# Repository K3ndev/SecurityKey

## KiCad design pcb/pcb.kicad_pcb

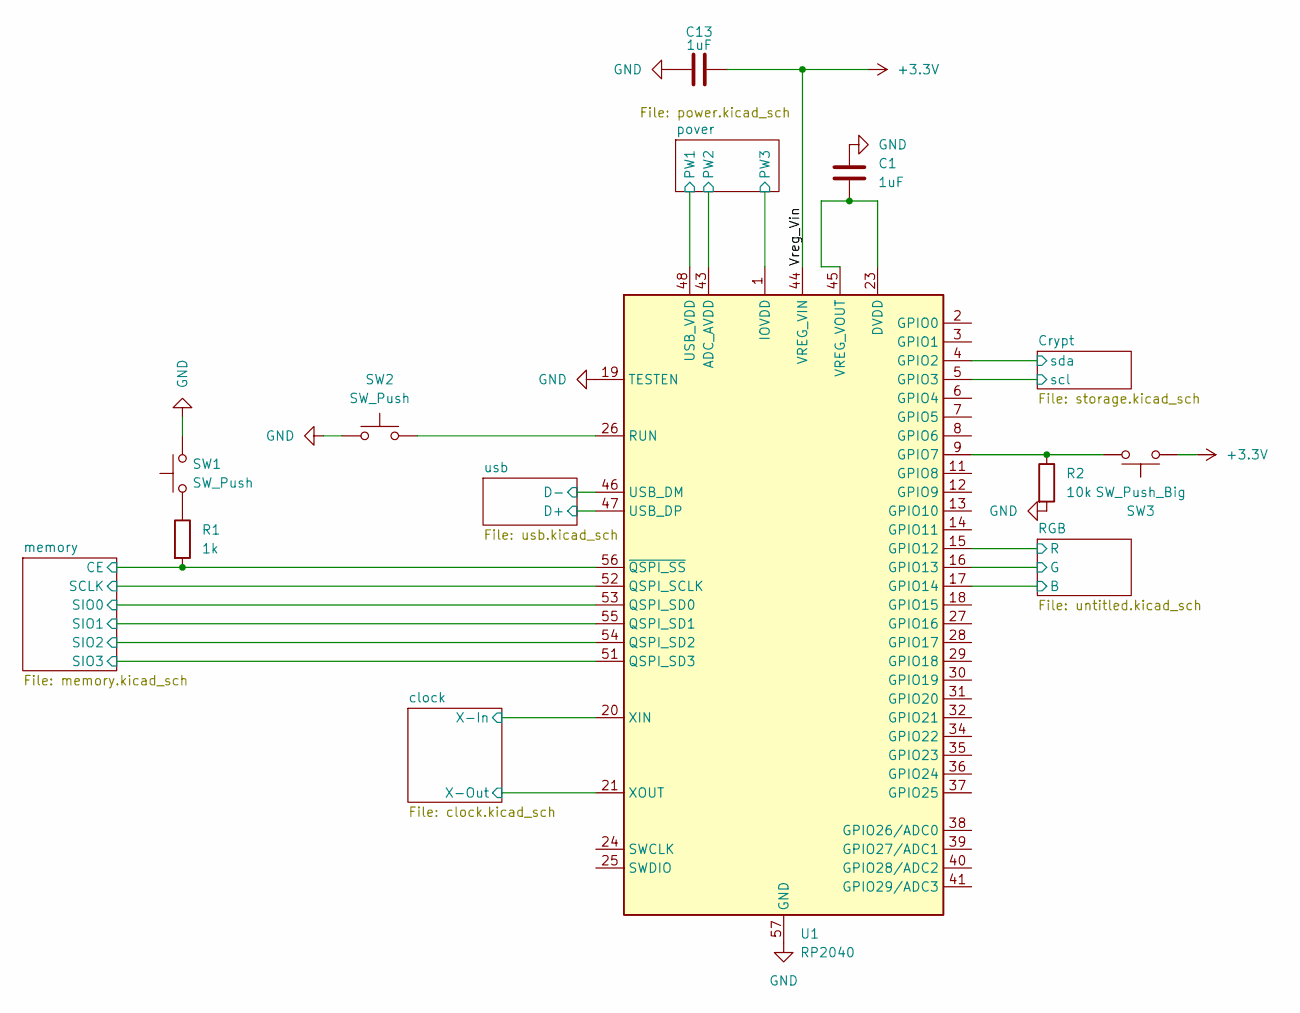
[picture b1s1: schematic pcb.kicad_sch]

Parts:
C1: 1uF; C_0603_1608Metric; LCSC Part C1592
C13: 1uF; C_0603_1608Metric; LCSC Part C1591
R1: 1k; R_0603_1608Metric; LCSC Part C22548
R2: 10k; R_0603_1608Metric; LCSC Part C98220
SW1, SW2: SW_Push; SW-SMD_L3.9-W3.0-P4.45; LCSC Part C115357
SW3: SW_Push_Big; SW-SMD_L3.9-W3.0-P4.45; LCSC Part C115357
U1: RP2040; QFN-56-1EP_7x7mm_P0.4mm_EP3.2x3.2mm; LCSC Part C2040

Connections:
+3.3V: C13.2, SW3.2, U1.1 (IOVDD), U1.10 (IOVDD), U1.22 (IOVDD), U1.33 (IOVDD), U1.42 (IOVDD), U1.43 (ADC_AVDD), U1.44 (VREG_VIN), U1.48 (USB_VDD), U1.49 (IOVDD); also elsewhere on the board
/Crypt/scl: U1.5 (GPIO3); also elsewhere on the board
/Crypt/sda: U1.4 (GPIO2); also elsewhere on the board
/RGB/B: U1.17 (GPIO14); also elsewhere on the board
/RGB/G: U1.16 (GPIO13); also elsewhere on the board
/RGB/R: U1.15 (GPIO12); also elsewhere on the board
/clock/X-In: U1.20 (XIN); also elsewhere on the board
/clock/X-Out: U1.21 (XOUT); also elsewhere on the board
/memory/CE: R1.2, U1.56 (~QSPI_SS); also elsewhere on the board
/memory/SCLK: U1.52 (QSPI_SCLK); also elsewhere on the board
/memory/SIO0: U1.53 (QSPI_SD0); also elsewhere on the board
/memory/SIO1: U1.55 (QSPI_SD1); also elsewhere on the board
/memory/SIO2: U1.54 (QSPI_SD2); also elsewhere on the board
/memory/SIO3: U1.51 (QSPI_SD3); also elsewhere on the board
/usb/D+: U1.47 (USB_DP); also elsewhere on the board
/usb/D-: U1.46 (USB_DM); also elsewhere on the board
GND: C1.2, C13.1, R2.2, SW1.2, SW2.1, U1.19 (TESTEN), U1.57 (GND); also elsewhere on the board
unnamed: R1.1, SW1.1
unnamed: R2.1, SW3.1, U1.9 (GPIO7)
unnamed: SW2.2, U1.26 (RUN)
unnamed: C1.1, U1.23 (DVDD), U1.45 (VREG_VOUT), U1.50 (DVDD)

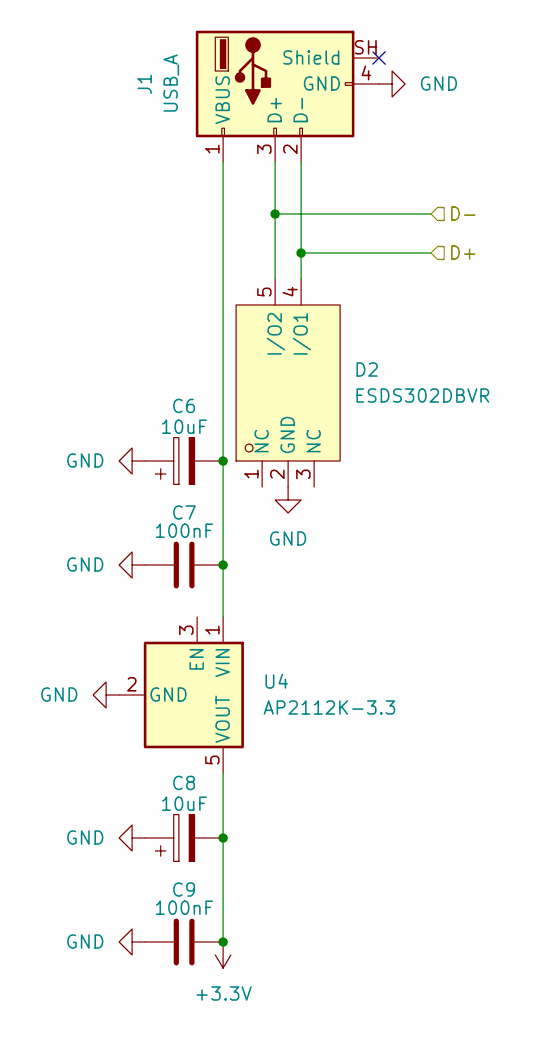
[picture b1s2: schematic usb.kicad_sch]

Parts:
C6, C8: 10uF; C_0603_1608Metric; LCSC Part C19702
C7, C9: 100nF; C_0603_1608Metric; LCSC Part C1591
D2: ESDS302DBVR; SOT-23-5_L3.0-W1.6-P0.95-LS2.8-BL; MPN ESDS302DBVR; LCSC Part C1975280
J1: USB_A; USB_A_PCB_Edge_receptacle
U4: AP2112K-3.3; SOT-23-5; LCSC Part C51118

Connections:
+3.3V: C8.2, C9.2, U4.5 (VOUT); also elsewhere on the board
/usb/D+: D2.4 (I/O1), J1.2 (D-); also elsewhere on the board
/usb/D-: D2.5 (I/O2), J1.3 (D+); also elsewhere on the board
GND: C6.1, C7.1, C8.1, C9.1, D2.2 (GND), J1.4 (GND), U4.2 (GND); also elsewhere on the board
unnamed: C6.2, C7.2, J1.1 (VBUS), U4.1 (VIN)

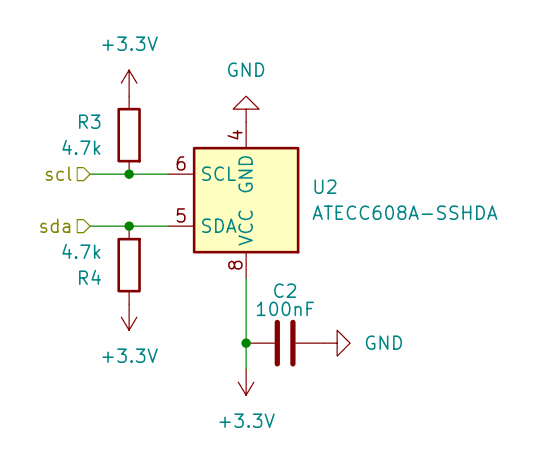
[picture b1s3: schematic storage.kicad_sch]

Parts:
C2: 100nF; C_0603_1608Metric; LCSC Part C1591
R3, R4: 4.7k; R_0603_1608Metric; LCSC Part C99782
U2: ATECC608A-SSHDA; SOIC-8_3.9x4.9mm_P1.27mm; LCSC Part C616024

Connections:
+3.3V: C2.1, R3.1, R4.1, U2.8 (VCC); also elsewhere on the board
/Crypt/scl: R3.2, U2.6 (SCL); also elsewhere on the board
/Crypt/sda: R4.2, U2.5 (SDA); also elsewhere on the board
GND: C2.2, U2.4 (GND); also elsewhere on the board

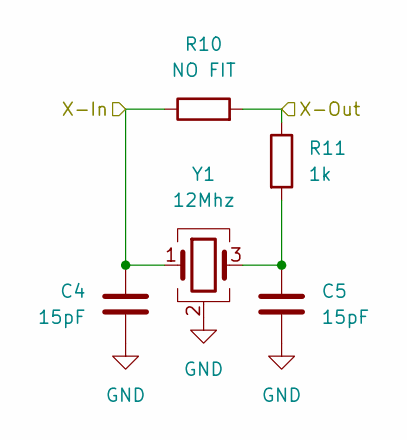
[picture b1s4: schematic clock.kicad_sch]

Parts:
C4, C5: 15pF; C_0603_1608Metric; LCSC Part C1644
R10: NO FIT; R_0603_1608Metric
R11: 1k; R_0603_1608Metric; LCSC Part C22548
Y1: 12Mhz; Crystal_SMD_3225-4Pin_3.2x2.5mm; LCSC Part C20625731

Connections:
/clock/X-In: C4.1, R10.1, Y1.1; also elsewhere on the board
/clock/X-Out: R10.2, R11.1; also elsewhere on the board
GND: C4.2, C5.2, Y1.2 (G), Y1.4 (G); also elsewhere on the board
unnamed: C5.1, R11.2, Y1.3

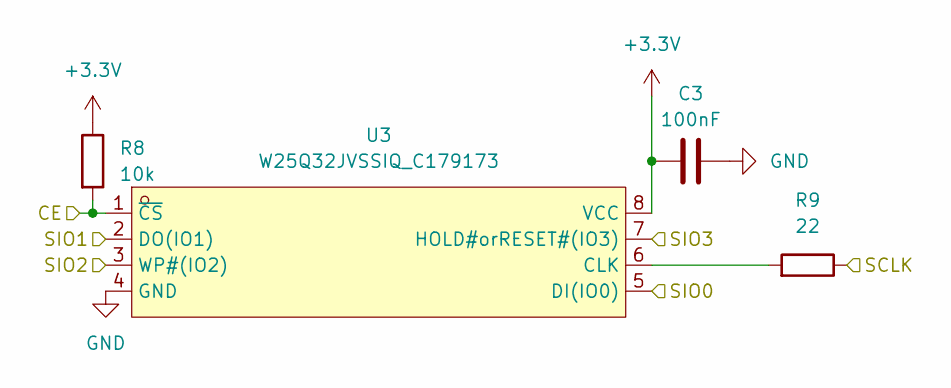
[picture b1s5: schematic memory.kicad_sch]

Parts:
C3: 100nF; C_0603_1608Metric; LCSC Part C1591
R8: 10k; R_0603_1608Metric; LCSC Part C98220
R9: 22; R_0603_1608Metric; LCSC Part C23345
U3: W25Q32JVSSIQ_C179173; SOIC-8_L5.3-W5.3-P1.27-LS8.0-BL; MPN W25Q32JVSSIQ; LCSC Part C179173

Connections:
+3.3V: C3.1, R8.1, U3.8 (VCC); also elsewhere on the board
/memory/CE: R8.2, U3.1 (~CS); also elsewhere on the board
/memory/SCLK: R9.1; also elsewhere on the board
/memory/SIO0: U3.5 (DI(IO0)); also elsewhere on the board
/memory/SIO1: U3.2 (DO(IO1)); also elsewhere on the board
/memory/SIO2: U3.3 (WP#(IO2)); also elsewhere on the board
/memory/SIO3: U3.7 (HOLD#orRESET#(IO3)); also elsewhere on the board
GND: C3.2, U3.4 (GND); also elsewhere on the board
unnamed: R9.2, U3.6 (CLK)

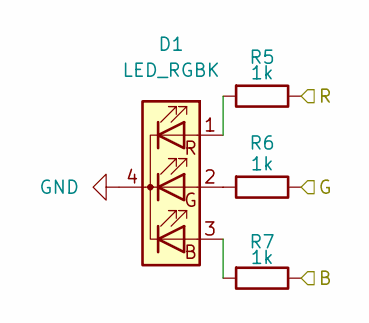
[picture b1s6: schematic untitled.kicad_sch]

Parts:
D1: LED_RGBK; LED_WS2812B_PLCC4_5.0x5.0mm_P3.2mm; LCSC Part C52917433
R5, R6, R7: 1k; R_0603_1608Metric; LCSC Part C22548

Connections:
/RGB/B: R7.1; also elsewhere on the board
/RGB/G: R6.1; also elsewhere on the board
/RGB/R: R5.1; also elsewhere on the board
GND: D1.4 (K); also elsewhere on the board
unnamed: D1.3 (BA), R7.2
unnamed: D1.2 (GA), R6.2
unnamed: D1.1 (RA), R5.2

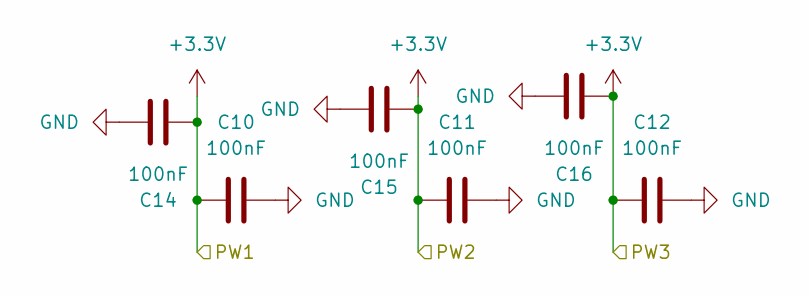
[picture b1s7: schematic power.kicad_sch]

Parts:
C10, C11, C12, C14, C15, C16: 100nF; C_0603_1608Metric; LCSC Part C1591

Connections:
+3.3V: C10.1, C11.1, C12.1, C14.1, C15.1, C16.1; also elsewhere on the board
GND: C10.2, C11.2, C12.2, C14.2, C15.2, C16.2; also elsewhere on the board

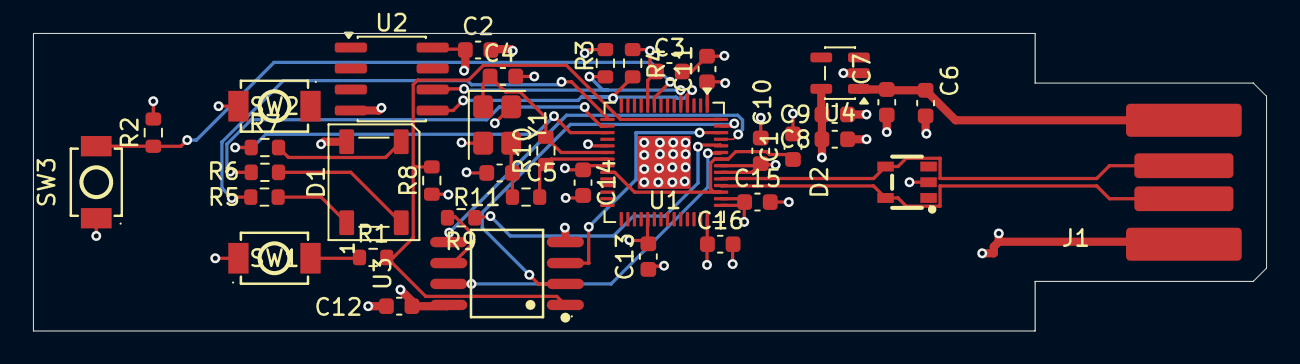
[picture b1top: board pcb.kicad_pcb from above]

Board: 4 copper layers, 74.6 x 18.0 mm, 38 parts (0 on the bottom side), 27 nets.
